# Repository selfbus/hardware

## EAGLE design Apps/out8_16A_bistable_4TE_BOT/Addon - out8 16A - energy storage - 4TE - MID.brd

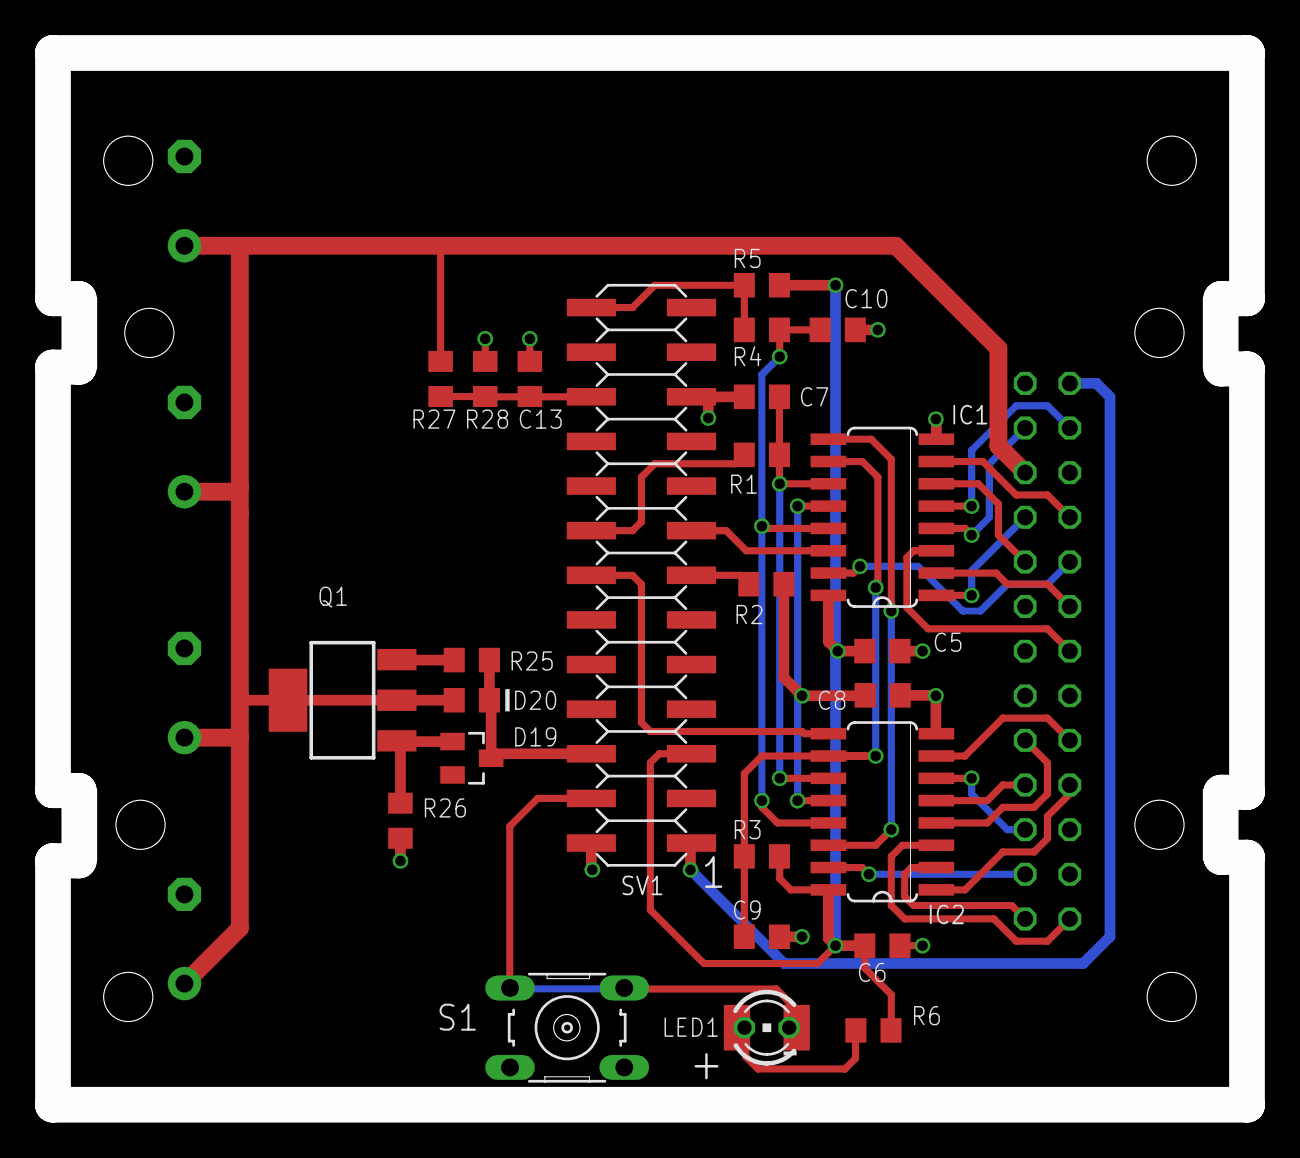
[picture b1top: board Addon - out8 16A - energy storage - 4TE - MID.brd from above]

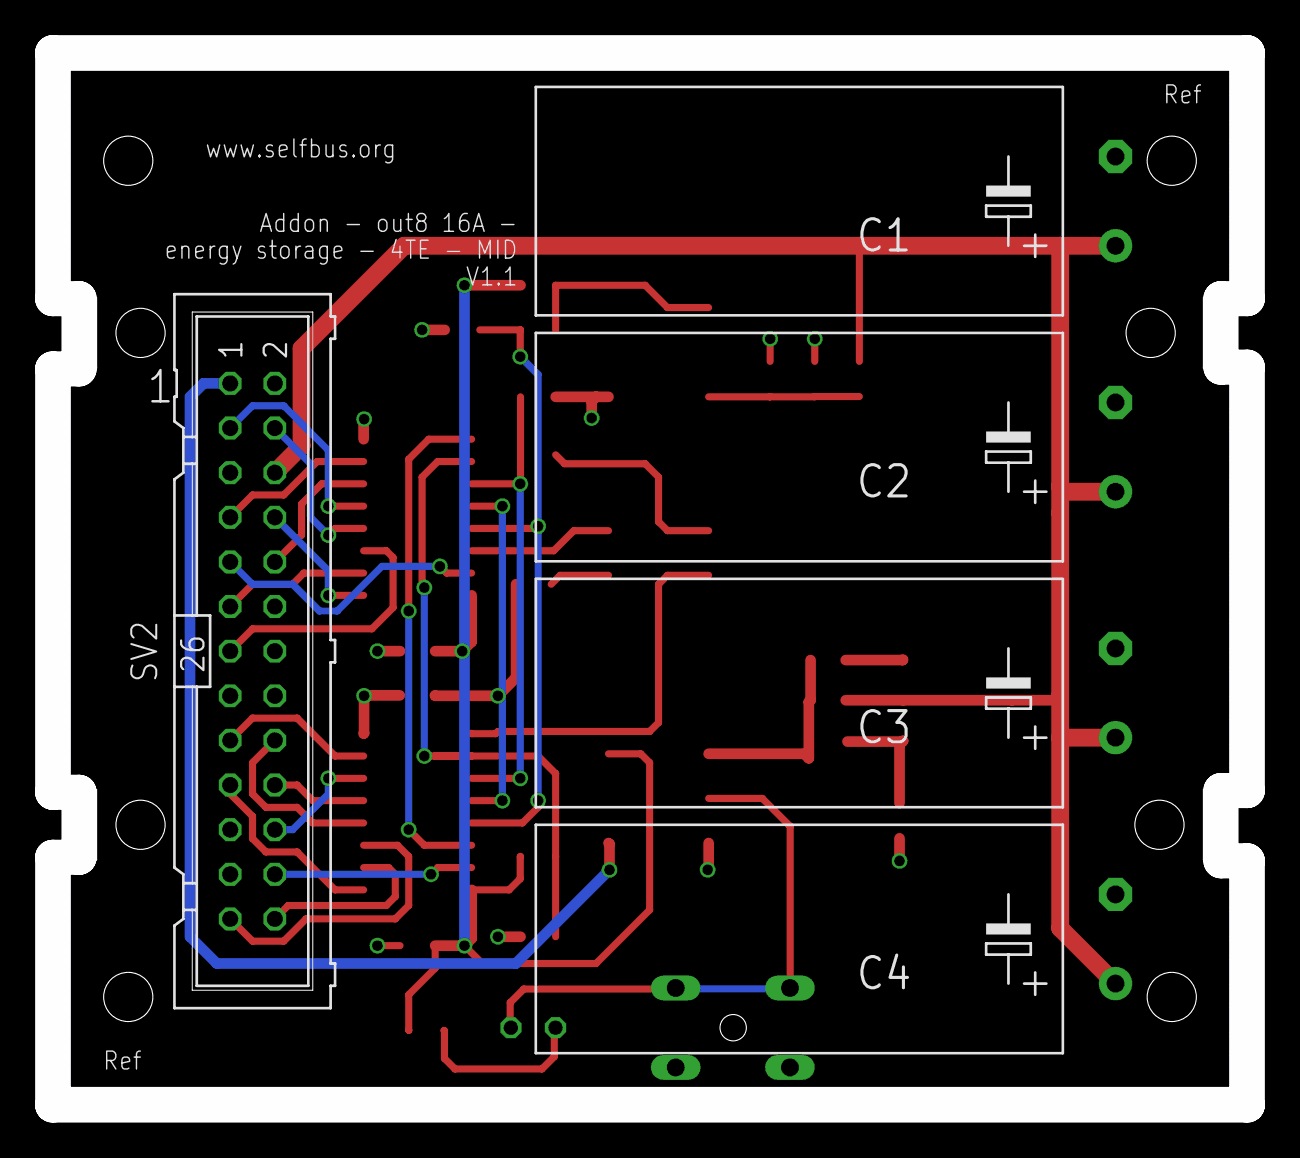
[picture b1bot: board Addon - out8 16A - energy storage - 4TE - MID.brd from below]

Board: 2 copper layers, 68.0 x 59.9 mm, 31 parts (5 on the bottom side), 36 nets.

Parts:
C1, C2, C3, C4: 1800µF 35V; E5-13-30
C5, C6, C9: 100n; R0805M
C7, C8, C10: 22p; R0805M
C13: 10n; R0805M
D19: 2,7V; SOT23
D20: TS4148; D0805
IC1, IC2: 74HC595D; SO16
LED1: red; LED3MM
LED2: LG_T679-E1F1-1; PLCC2
Q1: BCP52; SOT223
R1, R2, R4, R25: 100R; R0805M
R3, R5: 10k; R0805M
R6: 1,5k; R0805M
R26: 100k; R0805M
R27: 36k 1%; R0805M
R28: 3k 1%; R0805M
S1: Prog; B3F-10XX
SV1: 2X13SMD
SV2: A; ML26

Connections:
/SSEL: R2.1, SV1.13
ADC_URAIL: C13.1, R27.1, R28.2, SV1.22
GND: C1.-, C2.-, C3.-, C4.-, C5.2, C6.2, C7.2, C8.2, C9.2, C10.2, C13.2, IC1.8, IC2.8, R26.1, R28.1, S1.1, S1.2, SV1.2, SV1.21, SV2.2
KNX: SV1.1, SV2.1
KNX_DC: D19.3, D20.C, R25.2, SV1.6
MISO: IC2.9, SV1.14
MOSI: IC1.14, SV1.15
unnamed: D19.1, Q1.1, R26.2
unnamed: IC1.9, IC2.14
unnamed: C7.1, IC1.11, IC2.11, R1.2
unnamed: C8.1, IC1.12, IC2.12, R2.2
unnamed: LED1.A, LED2.A, R6.2
unnamed: Q1.3, R25.1
unnamed: C10.1, IC1.13, IC2.13, R4.2
unnamed: C9.1, IC1.10, IC2.10, R3.1
OFF_1: IC1.15, SV2.9
OFF_2: IC1.2, SV2.11
OFF_3: IC1.4, SV2.4
OFF_4: IC1.6, SV2.10
OFF_5: IC2.15, SV2.24
OFF_6: IC2.2, SV2.26
OFF_7: IC2.4, SV2.18
OFF_8: IC2.6, SV2.22
ON__1: IC1.1, SV2.8
ON__2: IC1.3, SV2.13
ON__3: IC1.5, SV2.3
ON__4: IC1.7, SV2.7
ON__5: IC2.1, SV2.19
ON__6: IC2.3, SV2.25
ON__7: IC2.5, SV2.20
ON__8: IC2.7, SV2.17
PROG: LED1.K, LED2.C, S1.3, S1.4, SV1.4
RELPWM: R4.1, R5.1, SV1.26
SCK: R1.1, SV1.16
VCC: C5.1, C6.1, IC1.16, IC2.16, R3.2, R5.2, R6.1, SV1.5
VCC_REL: C1.+, C2.+, C3.+, C4.+, D20.A, Q1.2, Q1.4, R27.2, SV2.6
